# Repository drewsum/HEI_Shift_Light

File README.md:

# HEI_Shift_Light
An automotive shift light meant to integrate into the TACH signal from an HEI distributor, to be embedded in a dashboard

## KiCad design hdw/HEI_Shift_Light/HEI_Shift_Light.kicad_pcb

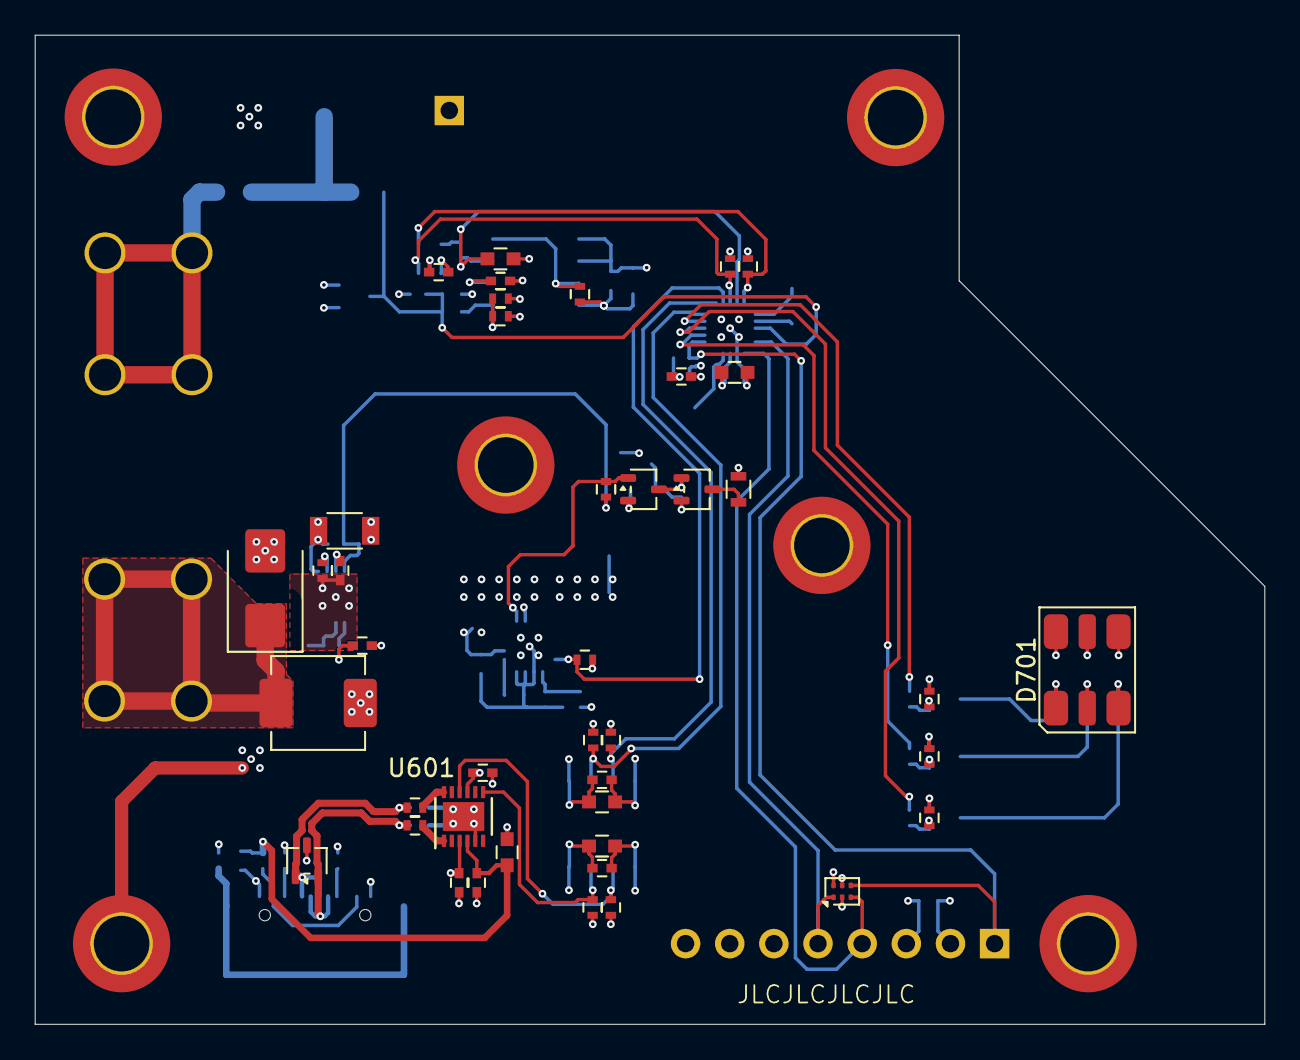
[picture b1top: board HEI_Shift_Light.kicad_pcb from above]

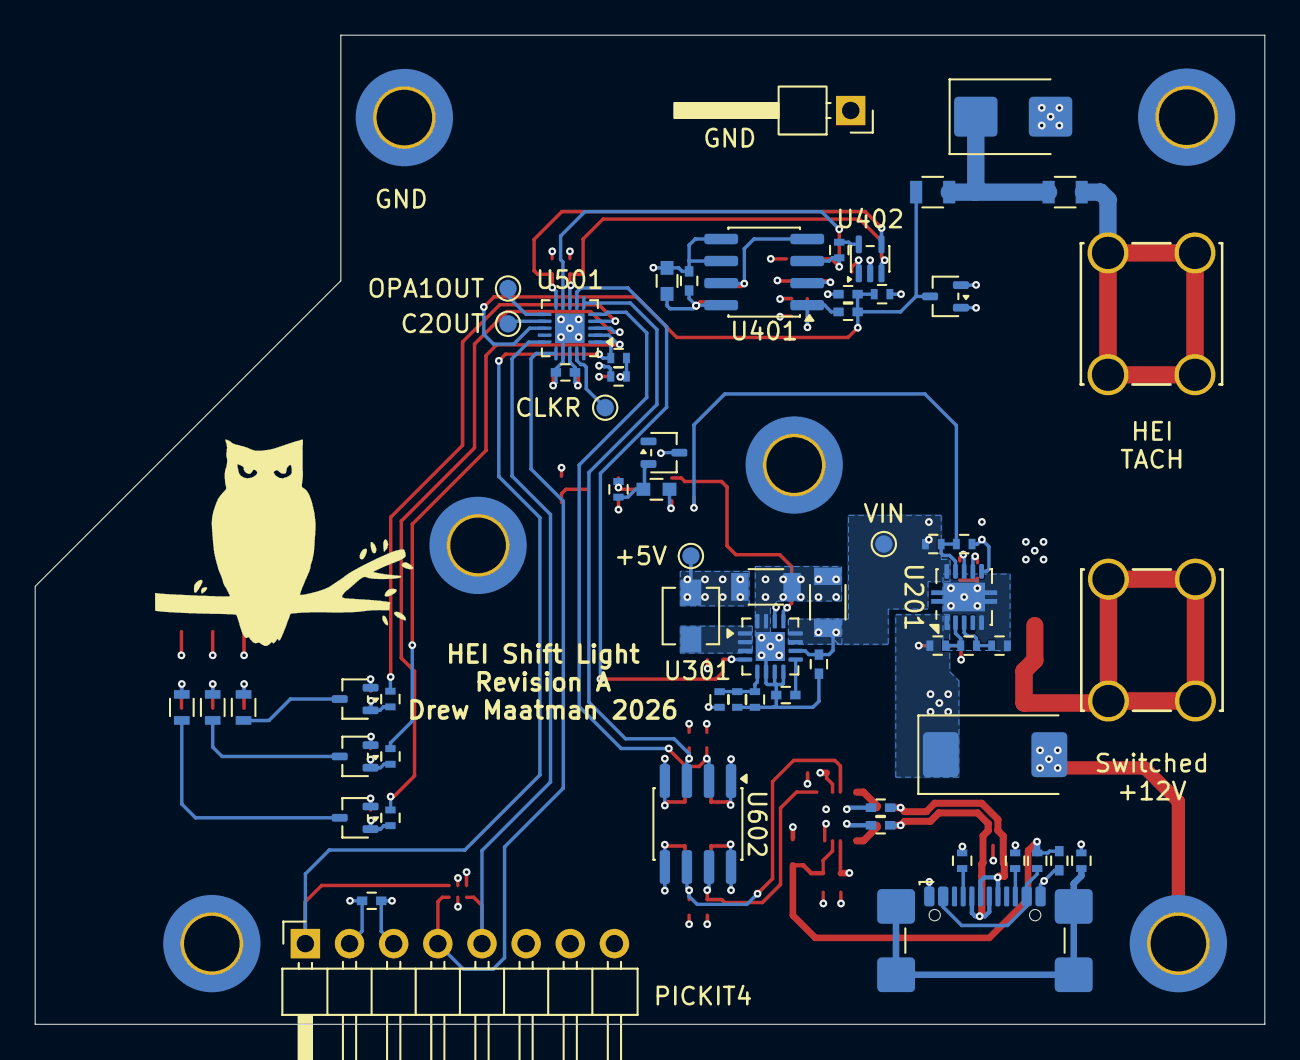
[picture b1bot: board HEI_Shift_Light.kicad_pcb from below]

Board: 4 copper layers, 70.7 x 56.9 mm, 111 parts (63 on the bottom side), 63 nets.

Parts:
C201: 100uF; CP_EIA-7343-43_Kemet-X
C202, C203, C303, C403, C404, C501, C502, C503, C601, C602, C604, C605, C609, C611: 0.1uF; C_0402
C204, C301: 10uF; C_1206
C302, C402, C405: 10nF; C_0402
C304: 22uF; C_1206
C305, C406, C407, C504, C603, C606, C610: 10uF; C_0603
C401: 3300pF; C_0402
C607, C608: 47pF; C_0402
D201, D401: TVS; D_SMB
D301, D402: BAT54SW; SOT-323_SC-70
D501: PESD5V0L4UF; SOT-886
D601: SP0502BAJTG; SOT-323_SC-70
D701: Inolux_IN-P55TATRGB; LED_Inolux_IN-P55TATRGB_PLCC6_5.0x5.5mm_P1.8mm
H801, H802, H803, H804, H813, H814: MountingHole_Pad; MountingHole_3.2mm_M3_DIN965_Pad_TopBottom
J201: VIN; CONN_7691_KEY
J401: TACH; CONN_7691_KEY
J501: PICKIT4; PICKIT4_Header
J601: USB_C_Receptacle_USB2.0_16P; USB_C_Receptacle_GCT_USB4110
L201: 10uH; L_Vishay_IHLP-2020
L301: 2.2uH; L_Vishay_IHLP-1212
L601, L602: 600R 0.5A; L_0402
Q301, Q302, Q701, Q702, Q703: DMN3150LW-7; SOT-323_SC-70
R201: 332k; R_0402
R202: 15k; R_0402
R203: 30.1k; R_0402
R204: 7.5k; R_0402
R205, R404, R405, R601, R602, R605, R606: 100k; R_0402
R206: 42.2k; R_0402
R301, R306, R406, R501, R503, R504, R704, R705, R706: 10k; R_0402
R302: 10; R_0402
R303: 0; R_0402
R304: 562k; R_0402
R305: 180k; R_0402
R307, R708: 150; R_0603
R401, R402: 10k; R_0805
R403: 5.6k; R_0402
R407: 133k; R_0402
R502: 1k; R_0402
R603, R604, R701, R702, R703: 27; R_0402
R607, R608: 5.1k; R_0402
R707, R709: 91; R_0603
TP201: GND; PinHeader_1x01_P2.54mm_Horizontal
TP202: VIN; TestPoint_Pad_D1.0mm
TP301: 5V; TestPoint_Pad_D1.0mm
TP501: C2OUT; TestPoint_Pad_D1.0mm
TP502: OPA1OUT; TestPoint_Pad_D1.0mm
TP503: CLKR; TestPoint_Pad_D1.0mm
U201: TPS26624DRCR; VSON-10-1EP_3x3mm_P0.5mm_EP1.65x2.4mm
U301: TPS62153; QFN-16-1EP_3x3mm_P0.5mm_EP1.675x1.675mm
U401: LM2907; SOIC-8_3.9x4.9mm_P1.27mm
U402: MCP4019-103ELT; SOT-353_SC-70-5
U501: PIC18F16Q41; VQFN-20-1EP_3x3mm_P0.4mm_EP1.7x1.7mm
U601: FT234XD; DFN-12-1EP_3x3mm_Pitch0.45mm
U602: ISO7321C; SOIC-8_3.9x4.9mm_P1.27mm

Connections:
+3.3V_USB: C601.1, C604.1, C609.1, C610.1, R605.1, R606.1, U601.3 (3V3OUT), U601.9 (VCCIO), U602.8 (VCC2)
+5V: C304.1, C403.1, C404.1, C407.1, C501.1, C502.1, C504.1, C605.1, C606.1, D301.3 (COM), D402.2 (K), D501.6 (K4), D701.4 (AG), D701.5 (AR), D701.6 (AB), J501.2, L301.2, R301.1, R304.1, R307.1, R404.1, R501.1, R503.1, R504.1, R601.1, R602.1, TP301.1 (1_1), U301.14 (VOS), U401.5 (COL), U401.6 (V+), U402.1 (VDD), U501.18 (VDD), U602.1 (VCC1)
+5V_USB: C602.1, C603.1, C611.1, L601.2, U601.4 (VCC)
/Input Power/VIN_BATT: D201.1, J201.1 (Pin_1_1), L201.1
/Input Power/VIN_FILT: C201.1, C202.1, L201.2, R201.1, U201.1 (IN)
/Input Signal/TACH_FILT: D401.1, R401.2, R402.1
/Input Signal/TACH_IN: J401.1 (Pin_1_1), R401.1
/USB UART Bridge/BRIDGE_USB+: R603.2, U601.12 (USBDP)
/USB UART Bridge/BRIDGE_USB-: R604.2, U601.1 (USBDM)
/USB UART Bridge/CONN_USB+: C607.1, D601.1 (K), J601.A6 (D+), J601.B6 (D+), R603.1
/USB UART Bridge/CONN_USB-: C608.1, D601.2 (K), J601.A7 (D-), J601.B7 (D-), R604.1
C2OUT: TP501.1 (1_1), U501.12 (RC1)
CLKR: TP503.1 (1_1), U501.19 (RA5)
GND: C201.2, C202.2, C204.2, C301.2, C302.2, C303.2, C304.2, C305.2, C401.2, C403.2, C404.2, C405.2, C406.2, C407.2, C501.2, C502.2, C503.2, C504.2, C605.2, C606.2, D201.2, D401.2, D402.1 (A), D501.2 (A), D501.5 (A), H801.1 (1_1), H802.1 (1_1), H803.1 (1_1), H804.1 (1_1), H813.1 (1_1), H814.1 (1_1), J501.3, Q301.2 (S), Q302.2 (S), Q701.2 (S), Q702.2 (S), Q703.2 (S), R206.2, R303.2, R305.2, R403.2, R405.2, R406.2, R704.2, R705.2, R706.2, TP201.1 (1_1), U201.6 (GND), U301.6 (AGND), U301.7 (FSW), U301.8 (DEF), U301.15 (PGND), U301.16 (PGND), U301.17 (EP), U401.8 (GND), U402.2 (VSS), U501.17 (VSS), U501.21 (EP), U602.4 (GND1)
GND_USB: C601.2, C602.2, C603.2, C604.2, C607.2, C608.2, C609.2, C610.2, C611.2, D601.3 (A), J601.A1 (GND), J601.A12 (GND), J601.B1 (GND), J601.B12 (GND), L602.2, R607.2, R608.2, U601.5 (GND), U601.13 (GND), U602.5 (GND2)
I2C_SCL: R503.2, U402.3 (SCL), U501.8 (RB6)
I2C_SDA: R504.2, U402.4 (SDA), U501.10 (RB4)
LED_B: R701.2, U501.4 (RC3)
LED_G: R703.2, U501.3 (RC4)
LED_R: R702.2, U501.2 (RC5)
unnamed: C503.1, R501.2, R502.2
unnamed: C305.1, D301.2 (K), R306.1
unnamed: D701.1 (KB), R707.1
unnamed: D701.3 (KG), R709.1
unnamed: D701.2 (KR), R708.1
unnamed: J601.A5 (CC1), R607.1
unnamed: J601.B5 (CC2), R608.1
unnamed: J601.SH (SHIELD), L602.1
unnamed: J601.A4 (VBUS), J601.A9 (VBUS), J601.B4 (VBUS), J601.B9 (VBUS), L601.1
unnamed: L301.1, U301.1 (SW), U301.2 (SW), U301.3 (SW)
unnamed: Q301.3 (D), Q302.1 (G), R306.2
unnamed: Q302.3 (D), R307.2
unnamed: Q701.3 (D), R707.2
unnamed: Q701.1 (G), R701.1, R704.1
unnamed: Q702.3 (D), R708.2
unnamed: Q702.1 (G), R702.1, R705.1
unnamed: Q703.3 (D), R709.2
unnamed: Q703.1 (G), R703.1, R706.1
unnamed: C203.1, U201.8 (DVDT)
unnamed: R204.1, U201.7 (ILIM)
unnamed: R202.2, R203.1, U201.3 (OVP)
unnamed: C203.2, R203.2, R204.2, U201.5 (RTN), U201.11 (PAD)
unnamed: R201.2, R202.1, U201.2 (UVLO)
unnamed: R303.1, R304.2, R305.1, U301.5 (FB)
unnamed: C302.1, U301.9 (SS/TR)
unnamed: C405.1, U401.2 (CP1)
unnamed: R406.1, U401.4 (EMIT), U401.7 (IN-)
unnamed: C402.2, R404.2, R405.1, U401.1 (TACH+)
unnamed: R407.2, U402.5 (W)
OPA1OUT: TP502.1 (1_1), U501.11 (RC2)
PIC18F_ICSPCLK: D501.1 (K1), J501.5, U501.15 (RA1)
PIC18F_ICSPDAT: D501.3 (K2), J501.4, U501.16 (RA0)
POS5_PGOOD: R301.2, U301.4 (PG), U501.7 (RB7)
POS5_RUN: Q301.1 (G), R302.1, U301.13 (EN)
TACH_ANALOG: C406.1, R407.1, U401.3 (CP2/IN+), U501.9 (RB5)
TACH_PULSE: C401.1, C402.1, D402.3 (COM), R402.2, R403.1, U501.13 (RC0)
USB_UART_RX: R602.2, U501.5 (RC6), U602.2 (OUTA)
USB_UART_RX_ISO: R605.2, U601.7 (TXD), U602.7 (INA)
USB_UART_TX: R601.2, U501.6 (RC7), U602.3 (INB)
USB_UART_TX_ISO: R606.2, U601.10 (RXD), U602.6 (OUTB)
VIN_PGOOD: R205.2, R206.1, R302.2, U201.9 (~FLT)
Vin: C204.1, C301.1, C303.1, R205.1, TP202.1 (1_1), U201.10 (OUT), U301.10 (AVIN), U301.11 (PVIN), U301.12 (PVIN)
~PIC18F_MCLR: D501.4 (K3), J501.1, R502.1, U501.1 (~MCLR/RA3)

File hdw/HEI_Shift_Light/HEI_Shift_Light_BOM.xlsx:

Reference | Value | Datasheet | Footprint | Qty | DNP | Digi-Key PN
C201 | 100uF | https://yageogroup.com/content/datasheet/asset/file/KEM_T207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 | Capacitor_Tantalum_SMD:CP_EIA-7343-43_Kemet-X | 1 |  | 399-13127-1-ND
C202,C203,C303,C403,C404,C501,C502,C503,C601,C602,C604,C605,C609,C611 | 0.1uF | https://product.tdk.com/en/system/files/dam/doc/product/capa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 | Capacitors_SMD:C_0402 | 14 |  | 445-5932-1-ND
C204,C301 | 10uF | https://mm.digikey.com/Volume0/opasdata/d220001/medias/docus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 | Capacitors_SMD:C_1206 | 2 |  | 1276-7031-1-ND
C302 | 10nF | https://mm.digikey.com/Volume0/opasdata/d220001/medias/docus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 | Capacitors_SMD:C_0402 | 1 |  | 1276-1028-1-ND
C304 | 22uF | https://mm.digikey.com/Volume0/opasdata/d220001/medias/docus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 | Capacitors_SMD:C_1206 | 1 |  | 1276-3148-1-ND
C305,C406,C407,C504,C603,C606,C610 | 10uF | https://search.murata.co.jp/Ceramy/image/img/A01X/G101/ENG/G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 | Capacitors_SMD:C_0603 | 7 |  | 445-C1608X5R1A106K080ACCT-ND
C401 | 3300pF | https://search.murata.co.jp/Ceramy/image/img/A01X/G101/ENG/G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 | Capacitors_SMD:C_0402 | 1 |  | 490-GRM1555C1H332GE01DTR-ND
C402,C405 | 10nF | https://www.yageo.com/en/Chart/Download/pdf/CC0603JRNPO9BN103 | Capacitors_SMD:C_0402 | 2 |  | 1276-1028-1-ND
C607,C608 | 47pF | https://www.yageo.com/en/Chart/Download/pdf/CC0402JRNPO9BN470 | Capacitors_SMD:C_0402 | 2 |  | 311-1021-1-ND
D201,D401 | TVS | https://www.vishay.com/docs/88392/smbj.pdf | Diode_SMD:D_SMB | 2 |  | SMBJ15CA
D301,D402 | BAT54SW | https://assets.nexperia.com/documents/data-sheet/BAT54W_SER.pdf | Package_TO_SOT_SMD:SOT-323_SC-70 | 2 |  | BAT54SWT1GOSCT-ND
D501 | PESD5V0L4UF | https://assets.nexperia.com/documents/data-sheet/PESDXL4UF_G_W.pdf | Package_TO_SOT_SMD:SOT-886 | 1 |  | 1727-5796-1-ND
D601 | SP0502BAJTG | http://www.littelfuse.com/~/media/files/littelfuse/technical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 | Package_TO_SOT_SMD:SOT-323_SC-70 | 1 |  | F3158CT-ND
D701 | Inolux_IN-P55TATRGB | https://www.inolux-corp.com/datasheet/SMDLED/RGB%20Top%20Vie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 | LED_SMD:LED_Inolux_IN-P55TATRGB_PLCC6_5.0x5.5mm_P1.8mm | 1 |  | 1830-1098-1-ND
H805,H806,H807,H808,H809,H810,H811,H812 | MountingScrew | https://apmhexseal.com/wp-content/uploads/APMShortCatalog-HE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 |  | 8 |  | 335-1156-ND
J201 | VIN | https://www.keyelco.com/userAssets/file/K75p73.pdf | Custom Footprints Library:CONN_7691_KEY | 1 |  | 36-7691-ND
J401 | TACH | https://www.keyelco.com/userAssets/file/K75p73.pdf | Custom Footprints Library:CONN_7691_KEY | 1 |  | 36-7691-ND
J501 | PICKIT4 | https://suddendocs.samtec.com/catalog_english/htsw_th.pdf | Custom Footprints Library:PICKIT4_Header | 1 |  | SAM1051-08-ND
J601 | USB_C_Receptacle_USB2.0_16P | https://www.usb.org/sites/default/files/documents/usb_type-c.zip | Connector_USB:USB_C_Receptacle_GCT_USB4110 | 1 |  | 2073-USB4110-GF-A-1-ND
L201 | 10uH | https://www.vishay.com/docs/34563/ihlp-2020cz-8a.pdf | Inductor_SMD:L_Vishay_IHLP-2020 | 1 |  | 541-IHLP2020CZER100M8ACT-ND
L301 | 2.2uH | https://www.vishay.com/docs/34535/ihlp-1212bz-5a.pdf | Inductors_SMD:L_Vishay_IHLP-1212 | 1 |  | 541-IHLP1212BZEV2R2M5ACT-ND
L601,L602 | 600R 0.5A | https://pim.murata.com/asset/pim4/ferriteBeadInductortypefil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 | Inductors_SMD:L_0402 | 2 |  | 490-5441-1-ND
MK801,MK802,MK803,MK804 | Standoff | https://www.keyelco.com/userAssets/file/K75p87.pdf |  | 4 |  | 36-24397-ND
Q301,Q302,Q701,Q702,Q703 | DMN3150LW-7 | https://www.infineon.com/dgdl/Infineon-BSS214NW-DS-v02_02-en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 | Package_TO_SOT_SMD:SOT-323_SC-70 | 5 |  | DMN3150LWDICT-ND
R201 | 332k | https://www.vishay.com/docs/20035/dcrcwe3.pdf | Resistors_SMD:R_0402 | 1 |  | 541-332KLCT-ND
R202 | 15k | https://www.vishay.com/docs/20035/dcrcwe3.pdf | Resistors_SMD:R_0402 | 1 |  | 541-15.0KLCT-ND
R203 | 30.1k | https://www.vishay.com/docs/20035/dcrcwe3.pdf | Resistors_SMD:R_0402 | 1 |  | 541-4109-1-ND
R204 | 7.5k | https://www.vishay.com/docs/20035/dcrcwe3.pdf | Resistors_SMD:R_0402 | 1 |  | 541-7.50KLCT-ND
R205,R404,R405,R601,R602,R605,R606 | 100k | https://www.vishay.com/docs/20035/dcrcwe3.pdf | Resistors_SMD:R_0402 | 7 |  | 541-100KLCT-ND
R206 | 42.2k | https://www.vishay.com/docs/20035/dcrcwe3.pdf | Resistors_SMD:R_0402 | 1 |  | 541-42.2KLCT-ND
R301,R306,R406,R501,R503,R504,R704,R705,R706 | 10k | https://www.vishay.com/docs/20035/dcrcwe3.pdf | Resistors_SMD:R_0402 | 9 |  | 541-10.0KLCT-ND
R302 | 10 | https://www.vishay.com/docs/20035/dcrcwe3.pdf | Resistors_SMD:R_0402 | 1 |  | 541-10.0LCT-ND
R303 | 0 | https://www.vishay.com/docs/20035/dcrcwe3.pdf | Resistors_SMD:R_0402 | 1 |  | 541-0.0JCT-ND
R307,R708 | 150 | https://www.vishay.com/docs/20035/dcrcwe3.pdf | Resistors_SMD:R_0603 | 2 |  | 541-4023-1-ND
R401,R402 | 10k | https://industrial.panasonic.com/cdbs/www-data/pdf/AQA0000/A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 | Resistors_SMD:R_0805 | 2 |  | P16059CT-ND
R403 | 5.6k | https://www.vishay.com/docs/20035/dcrcwe3.pdf | Resistors_SMD:R_0402 | 1 |  | 541-5.60KLCT-ND
R407 | 133k | https://www.vishay.com/docs/20035/dcrcwe3.pdf | Resistors_SMD:R_0402 | 1 |  | 541-133KLCT-ND
R502 | 1k | https://www.vishay.com/docs/20035/dcrcwe3.pdf | Resistors_SMD:R_0402 | 1 |  | 541-1.00KLCT-ND
R603,R604,R701,R702,R703 | 27 | https://www.vishay.com/docs/20035/dcrcwe3.pdf | Resistors_SMD:R_0402 | 5 |  | 541-4082-1-ND
R607,R608 | 5.1k | https://www.vishay.com/docs/20035/dcrcwe3.pdf | Resistors_SMD:R_0402 | 2 |  | 541-5.10KLCT-ND
R707,R709 | 91 | https://www.vishay.com/docs/20035/dcrcwe3.pdf | Resistors_SMD:R_0603 | 2 |  | 541-CRCW060391R0FKEACCT-ND
TP201 | GND | https://suddendocs.samtec.com/catalog_english/htsw_th.pdf | Connector_PinHeader_2.54mm:PinHeader_1x01_P2.54mm_Horizontal | 1 |  | SAM1051-01-ND
U201 | TPS26624DRCR | https://www.ti.com/lit/gpn/tps2662 | Package_SON:VSON-10-1EP_3x3mm_P0.5mm_EP1.65x2.4mm | 1 |  | TPS26624DRCR-ND
U301 | TPS62153 | https://www.ti.com/lit/ds/symlink/tps62150.pdf?&ts=1589125931316 | Package_DFN_QFN:QFN-16-1EP_3x3mm_P0.5mm_EP1.675x1.675mm | 1 |  | 296-30010-1-ND
U401 | LM2907 | https://www.ti.com/lit/ds/symlink/lm2917-n.pdf | Package_SO:SOIC-8_3.9x4.9mm_P1.27mm | 1 |  | LM2907MX-8/NOPBCT-ND
U402 | MCP4019-103ELT | http://ww1.microchip.com/downloads/en/DeviceDoc/22147a.pdf | Package_TO_SOT_SMD:SOT-353_SC-70-5 | 1 |  | MCP4019T-103E/LTCT-ND
U501 | PIC18F16Q41 | https://ww1.microchip.com/downloads/aemDocuments/documents/M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 | Package_DFN_QFN:VQFN-20-1EP_3x3mm_P0.4mm_EP1.7x1.7mm | 1 |  | 150-PIC18F16Q41-I/REB-ND
U601 | FT234XD | http://www.ftdichip.com/Support/Documents/DataSheets/ICs/DS_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 | Housings_DFN_QFN:DFN-12-1EP_3x3mm_Pitch0.45mm | 1 |  | 768-1178-1-ND
U602 | ISO7321C | http://www.ti.com/general/docs/lit/getliterature.tsp?generic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 | Package_SO:SOIC-8_3.9x4.9mm_P1.27mm | 1 |  | 296-42102-1-ND

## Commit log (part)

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2026-05-23 started hardware project
2026-05-23 Added input power filtering
2026-05-24 more schematic progress
2026-05-30 populated input protection circuit passive components, updated PIC pinout, added stuff to frequency to voltage converter circuit
2026-05-30 added more shit, RGD LED, LC input filter
2026-06-01 filled in digikey part numbers
2026-06-01 fixed a few digikey pns
2026-06-02 Added input signal path simulation
2026-06-02 change LM2907 filter cap to 10uF
2026-06-02 fixed some digikey pns
2026-06-03 moved GND connections to mount holes, updated gitignore
2026-06-03 added component datasheet properties
2026-06-03 updated a lot of font, table of contents
2026-06-07 cleaned up digikey pns
2026-06-08 fixed some footprints, pulled into PCB
2026-06-08 Added dashboard PCB reference data
2026-06-08 arranged components in PCB
2026-06-09 added stackup, design rules
2026-06-09 fix some netclass issues
2026-06-09 started rough routing
2026-06-10 added reference photos
2026-06-10 came up with rough component placement
2026-06-13 Added indicator insert
2026-06-20 Verified board outline against dash mechanical constraints
2026-06-23 routed most of board
2026-06-23 finished routing
2026-06-23 added silkscreen project description, DRC checks
